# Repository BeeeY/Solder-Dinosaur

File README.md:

# Solder-Dinosaur
A pcb made in kicad of the shape of a dinosaur with flashing light up eyes.

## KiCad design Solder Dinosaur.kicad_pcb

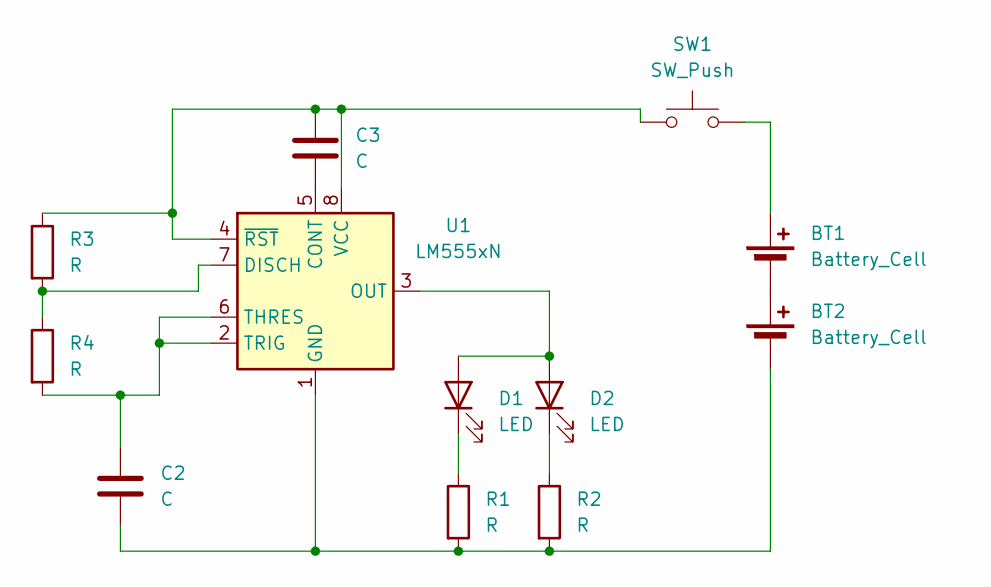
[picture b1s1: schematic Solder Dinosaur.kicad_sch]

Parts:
BT1, BT2: Battery_Cell; BatteryHolder_Keystone_3034_1x20mm
C2, C3: C; CP_Radial_D8.0mm_P5.00mm
D1, D2: LED; LED_D5.0mm
R1, R2, R3, R4: R; R_Axial_DIN0207_L6.3mm_D2.5mm_P7.62mm_Horizontal
SW1: SW_Push; SW_PUSH_6mm
U1: LM555xN; DIP-8_W7.62mm

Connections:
unnamed: BT1.1 (+), SW1.2
unnamed: BT1.2 (-), BT2.1 (+)
unnamed: BT2.2 (-), C2.2, R1.2, R2.2, U1.1 (GND)
unnamed: D1.2 (A), D2.2 (A), U1.3 (OUT)
unnamed: D1.1 (K), R1.1
unnamed: D2.1 (K), R2.1
unnamed: C3.2, U1.5 (CONT)
unnamed: R3.2, R4.1, U1.7 (DISCH)
unnamed: C2.1, R4.2, U1.2 (TRIG), U1.6 (THRES)
unnamed: C3.1, R3.1, SW1.1, U1.4 (~RST), U1.8 (VCC)

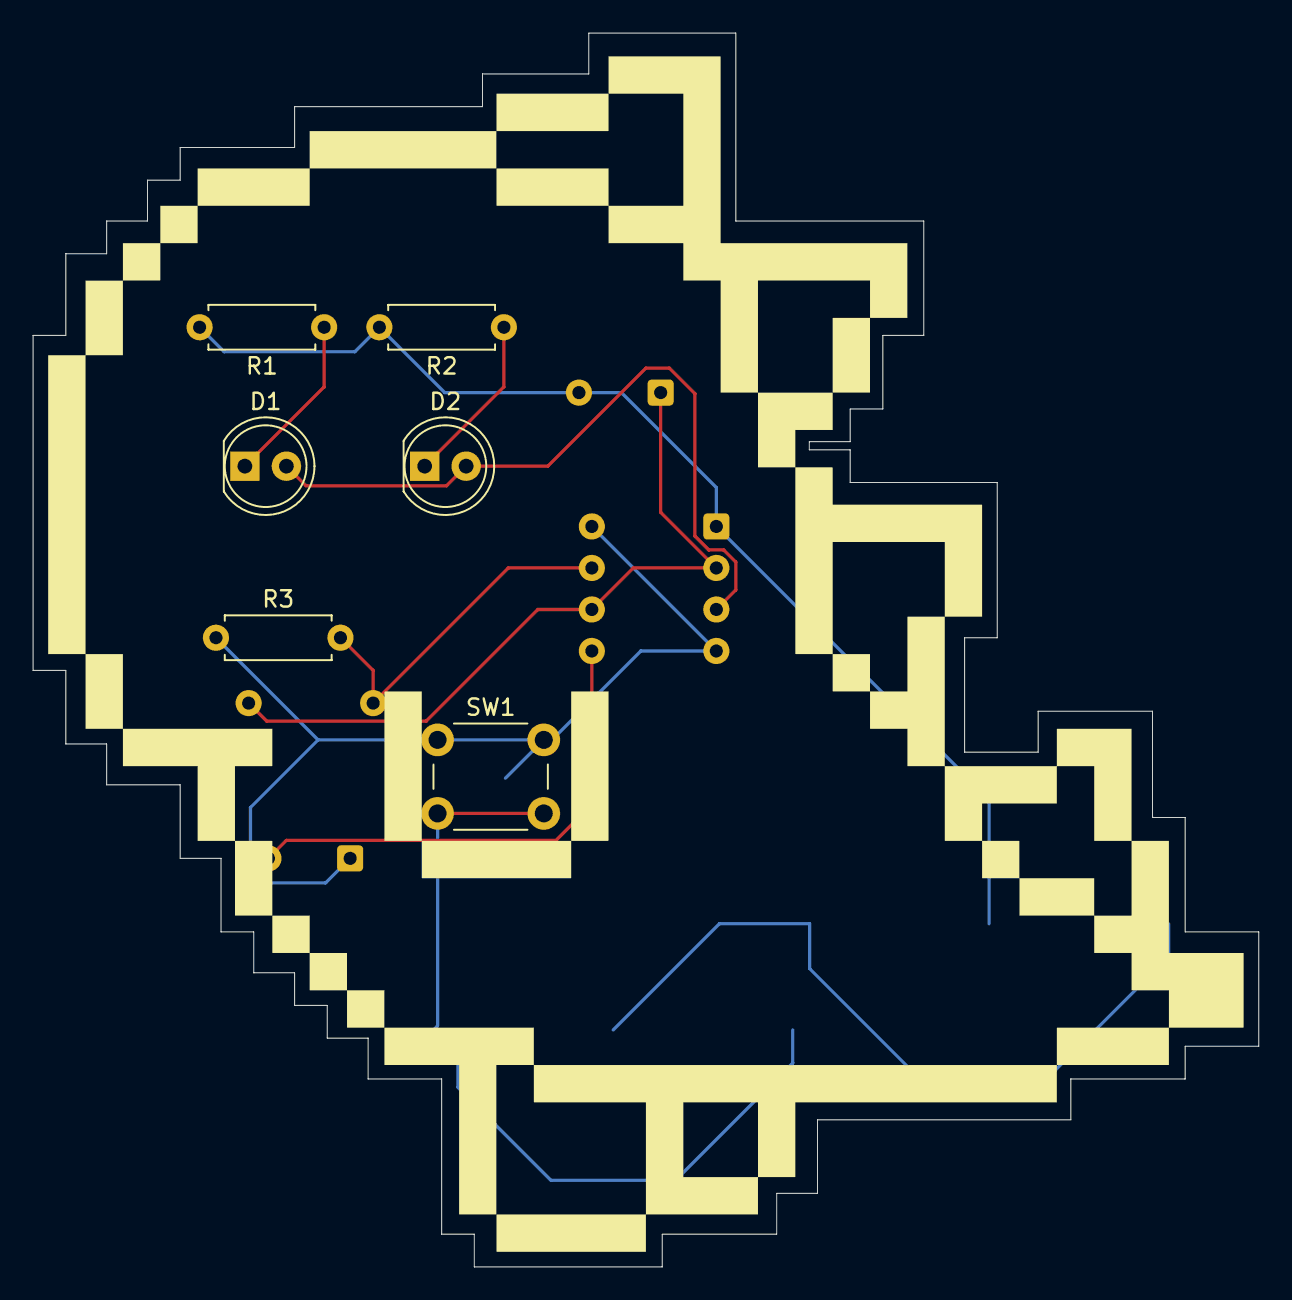
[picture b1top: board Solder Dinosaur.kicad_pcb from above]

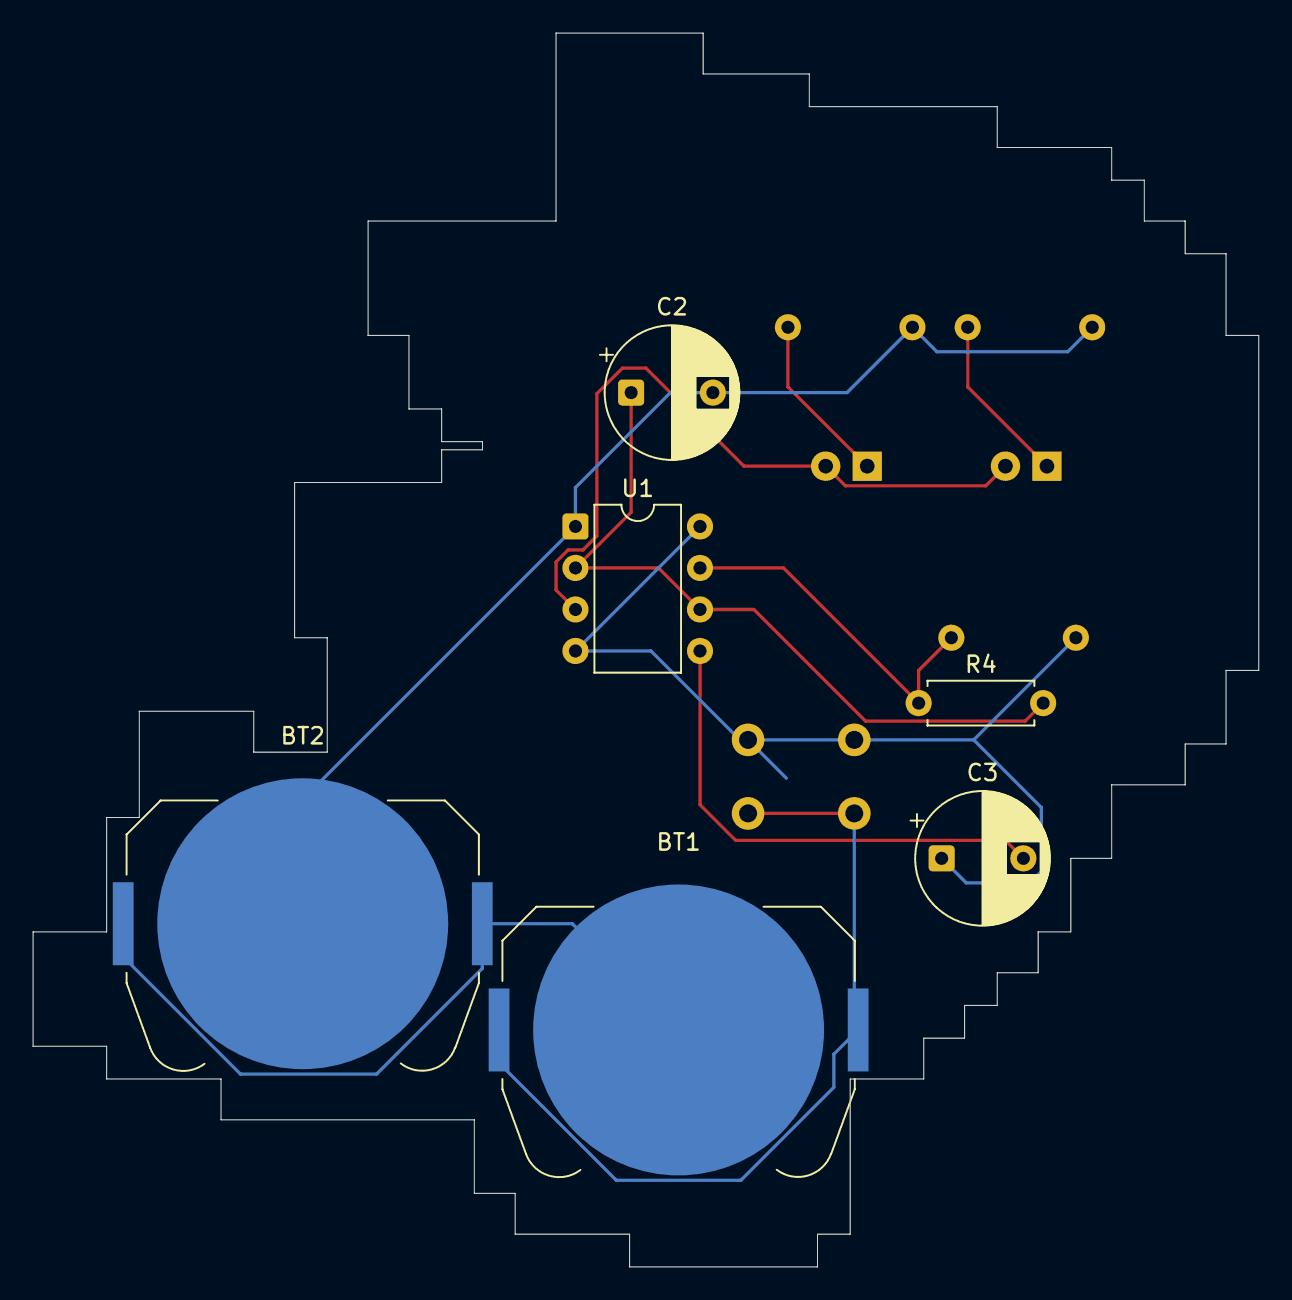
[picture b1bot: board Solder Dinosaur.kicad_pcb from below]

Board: 2 copper layers, 75.0 x 75.5 mm, 12 parts (6 on the bottom side), 10 nets.
